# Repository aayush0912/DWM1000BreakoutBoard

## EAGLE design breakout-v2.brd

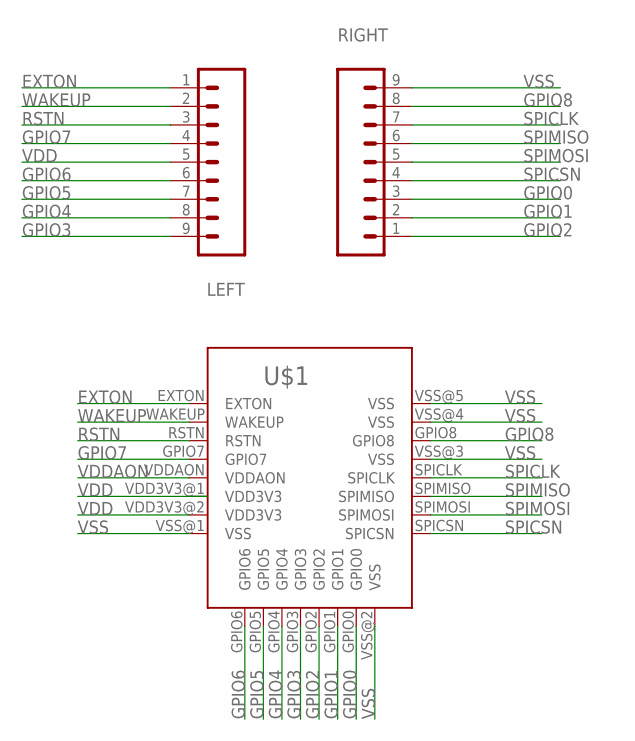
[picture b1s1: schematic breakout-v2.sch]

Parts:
LEFT: M09; 1X09
RIGHT: M09; 1X09
U$1: DWM1000

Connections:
EXTON: LEFT.1, U$1.EXTON
GPIO0: RIGHT.3, U$1.GPIO0
GPIO1: RIGHT.2, U$1.GPIO1
GPIO2: RIGHT.1, U$1.GPIO2
GPIO3: LEFT.9, U$1.GPIO3
GPIO4: LEFT.8, U$1.GPIO4
GPIO5: LEFT.7, U$1.GPIO5
GPIO6: LEFT.6, U$1.GPIO6
GPIO7: LEFT.4, U$1.GPIO7
GPIO8: RIGHT.8, U$1.GPIO8
RSTN: LEFT.3, U$1.RSTN
SPICLK: RIGHT.7, U$1.SPICLK
SPICSN: RIGHT.4, U$1.SPICSN
SPIMISO: RIGHT.6, U$1.SPIMISO
SPIMOSI: RIGHT.5, U$1.SPIMOSI
VDD: LEFT.5, U$1.VDD3V3@2 (VDD3V3)
VDD3V3: U$1.VDD3V3@1 (VDD3V3)
VDDAON: U$1.VDDAON
VSS: RIGHT.9, U$1.VSS@1 (VSS), U$1.VSS@2 (VSS), U$1.VSS@3 (VSS), U$1.VSS@4 (VSS), U$1.VSS@5 (VSS)
WAKEUP: LEFT.2, U$1.WAKEUP

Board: 2 copper layers, 3 parts (0 on the bottom side), 18 nets, no tracks yet.

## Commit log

2016-03-05 breakout board and part
2016-03-08 updated pad positions and re-arranged wires
2016-03-09 breakout board v2

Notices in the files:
parts and their libraries:
SparkFun-Connectors: Licensing: Creative Commons ShareAlike 4.0 International - https://creativecommons.org/licenses/by-sa/4.0
